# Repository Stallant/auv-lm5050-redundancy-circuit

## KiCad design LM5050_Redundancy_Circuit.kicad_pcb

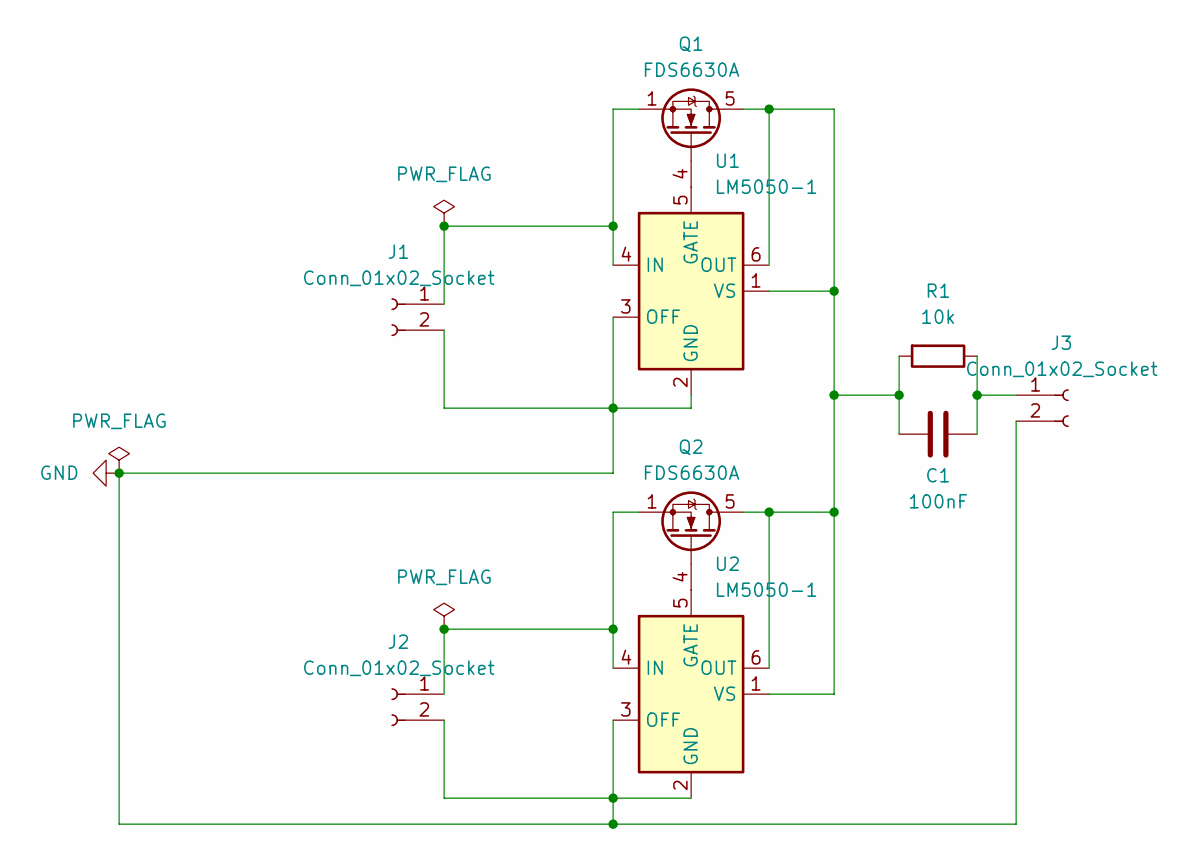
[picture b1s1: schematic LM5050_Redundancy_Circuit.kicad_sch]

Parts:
C1: 100nF; C_0805_2012Metric
J1, J2, J3: Conn_01x02_Socket; PinHeader_1x02_P2.54mm_Vertical
Q1, Q2: FDS6630A; SOIC-8_3.9x4.9mm_P1.27mm
R1: 10k; R_0805_2012Metric
U1, U2: LM5050-1; TSOT-23-6

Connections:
GND: J1.2, J2.2, J3.2, U1.2 (GND), U1.3 (OFF), U2.2 (GND), U2.3 (OFF)
unnamed: J1.1, Q1.1 (S), Q1.2 (S), Q1.3 (S), U1.4 (IN)
unnamed: J2.1, Q2.1 (S), Q2.2 (S), Q2.3 (S), U2.4 (IN)
unnamed: C1.1, J3.1, R1.1
unnamed: Q1.4 (G), U1.5 (GATE)
unnamed: Q2.4 (G), U2.5 (GATE)
unnamed: C1.2, Q1.5 (D), Q1.6 (D), Q1.7 (D), Q1.8 (D), Q2.5 (D), Q2.6 (D), Q2.7 (D), Q2.8 (D), R1.2, U1.1 (VS), U1.6 (OUT), U2.1 (VS), U2.6 (OUT)

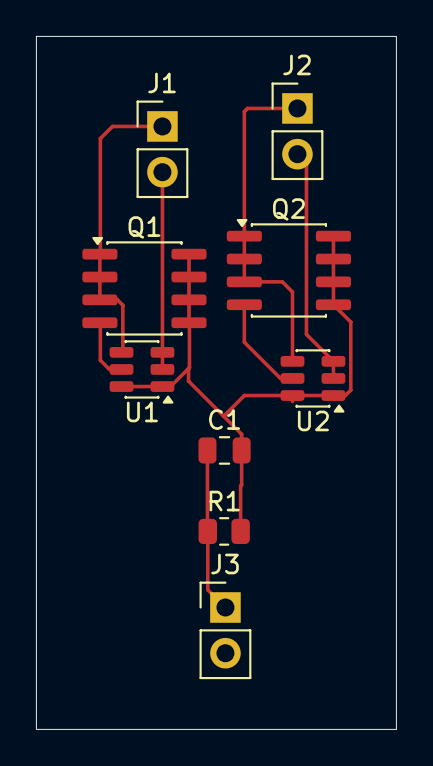
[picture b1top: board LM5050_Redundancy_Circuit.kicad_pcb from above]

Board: 2 copper layers, 20.0 x 38.5 mm, 9 parts (0 on the bottom side), 7 nets.

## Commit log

2026-06-29 Update project
